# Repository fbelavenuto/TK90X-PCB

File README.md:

# TK90X-PCB

Recriação da placa de circuito impresso do microcomputador de 8 bits TK90X da Microdigital. Projeto iniciado em setembro de 2020.

## Agradecimentos

Agradecimentos ao Daniel Viana (Danjovic) pelo desenho do esquema no software Eagle, Manoel Carvalho (Neco) pelo encorajamento e scans limpos da PCB e ao grupo [Clube do TK](https://www.facebook.com/groups/clubedotk) do Facebook.

## Revisões

Nesse repositório existem várias revisões relacionadas abaixo, cada revisão contém modificações em relação à revisão anterior.

### Rev. 3

Réplica da placa Rev. 3 da Microdigital (Silk TK90X-B rev 3). Essa versão é para montagem de uma réplica da placa original, sem modificações.

### Rev. 4

As modificações efetuadas são:
- Jumpers de solda para selecionar o tipo de memória DRAM, roteando a alimentação corretamente,
- Jumper de solda para permitir o uso de uma EPROM no lugar da ROM original.

### Rev. 5

As modificações efetuadas são:
- Jumpers de solda nos conectores EAR e MIC para opção de montagem com Jacks P2 mono ou estéreo e saída de áudio no conector MIC
-  Desativação do circuito de RF dando lugar a uma saída de vídeo-composto on-board e conector RCA próprio.

Essa revisão não é encorajada a ser fabricada.

### Rev. 6

As modificações efetuadas são:
- Alteração no IC10 para corrigir a leitura da porta 254, compatibilizando esta porta com o padrão ZX e permitindo a execução de mais softwares.

Alguns componentes não precisam ser montados pela extinção do circuito de RF, veja a documentação específica na pasta *Docs* da revisão.

### Rev. 7

As modificações efetuadas são:
- Alteração nos componentes do circuito de vídeo:
  - Retirados os componentes não necessários referente ao circuito de RF,
  - IC12 foi rotacionado para abrir espaço para um conector RCA extra.
- Adicionado conectores dupont/pinheader:
  - Botão de RESET externo,
  - Chave para seleção de frequência vertical da ULA,
  - LED para uso no gabinete do TK95.
- Jumper de solda para seleção do tipo de sinal de vídeo a ser codificado (NTSC ou PAL/PAL-M) de acordo com o valor de cristal escolhido.
- Jumper de solda para permitir a ligação do sinal necessário para uso da interface [TK-MEM 128K](http://www.luccas.com.br/index.php/8-bits/artigos/23-preparando-o-tk90x-tk95-para-a-tkmem-128).

O conector RCA extra está posicionado no mesmo lugar da saída de RF do ZX Spectrum original, permitindo a montagem da placa dentro do seu gabinete original. Este conector extra é configurado por um jumper de solda que permite mapear o sinal de vídeo ou o sinal de áudio dando a opção de colocar um segundo RCA adaptando o case de um TK90X e ter saída de áudio em RCA.

# Pastas

*Common* possui arquivos referentes a todas as revisões.

Dentro de cada pasta de cada revisão há três subpastas com os nomes *Docs*, *Eagle* e *Gerber*. O esquema elétrico em PDF, imagens, lista de materiais, etc, estão em *Docs*. Na subpasta *Eagle* há os arquivos originais para a versão 9 do software Autodesk Eagle. Para a confecção das placas há os arquivos em formato gerber na pasta *Gerber* que podem ser enviados para uma empresa de fabricação de PCBs.

Para a Rev.7 abra o arquivo [ibom.html](Rev7/Docs/ibom.html) localmente ou acesse [este link](https://fbelavenuto.github.io/pages/TK90X-PCB-Rev7-ibom.html) para visualizar os componentes e seus lugares na placa. Criado com o projeto [InteractiveHtmlBom](https://github.com/openscopeproject/InteractiveHtmlBom), linha de comando: `generate_interactive_bom --highlight-pin1 all --blacklist-empty-val TK90X.brd`

# Observações

É encorajado a fabricação da Rev. 7 por conter mais opções de configuração e correções de problemas conhecidos.

É recomendado a fabricação com finalização ENIG ou ouro no conector Edge para mais durabilidade.

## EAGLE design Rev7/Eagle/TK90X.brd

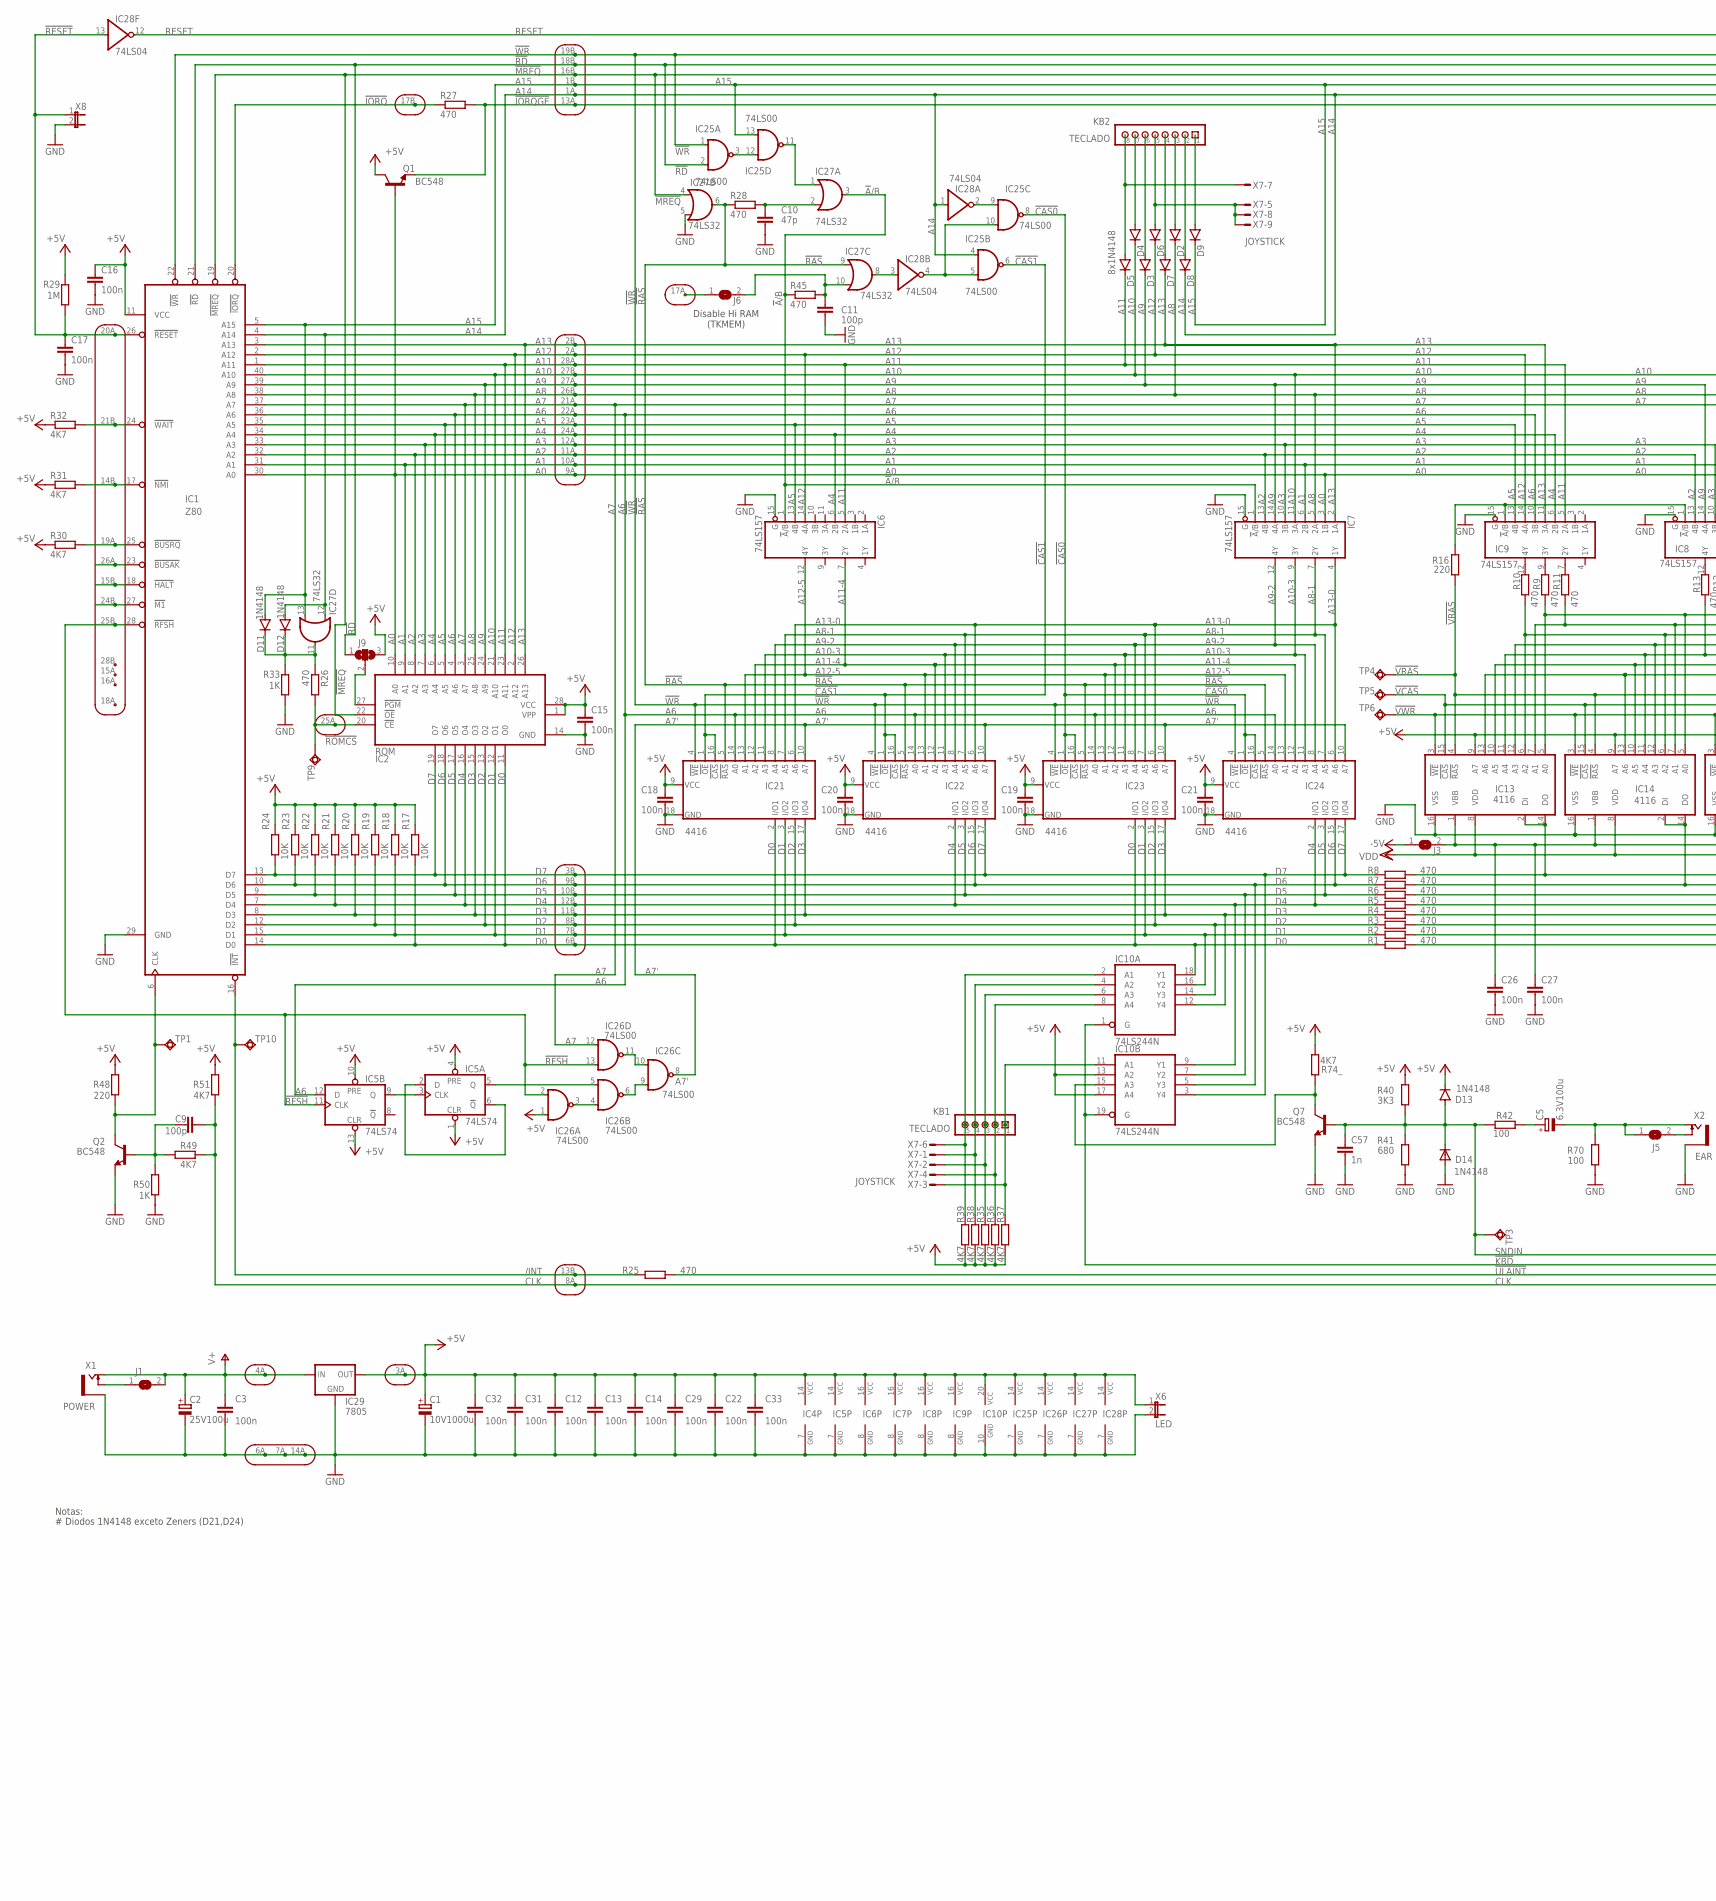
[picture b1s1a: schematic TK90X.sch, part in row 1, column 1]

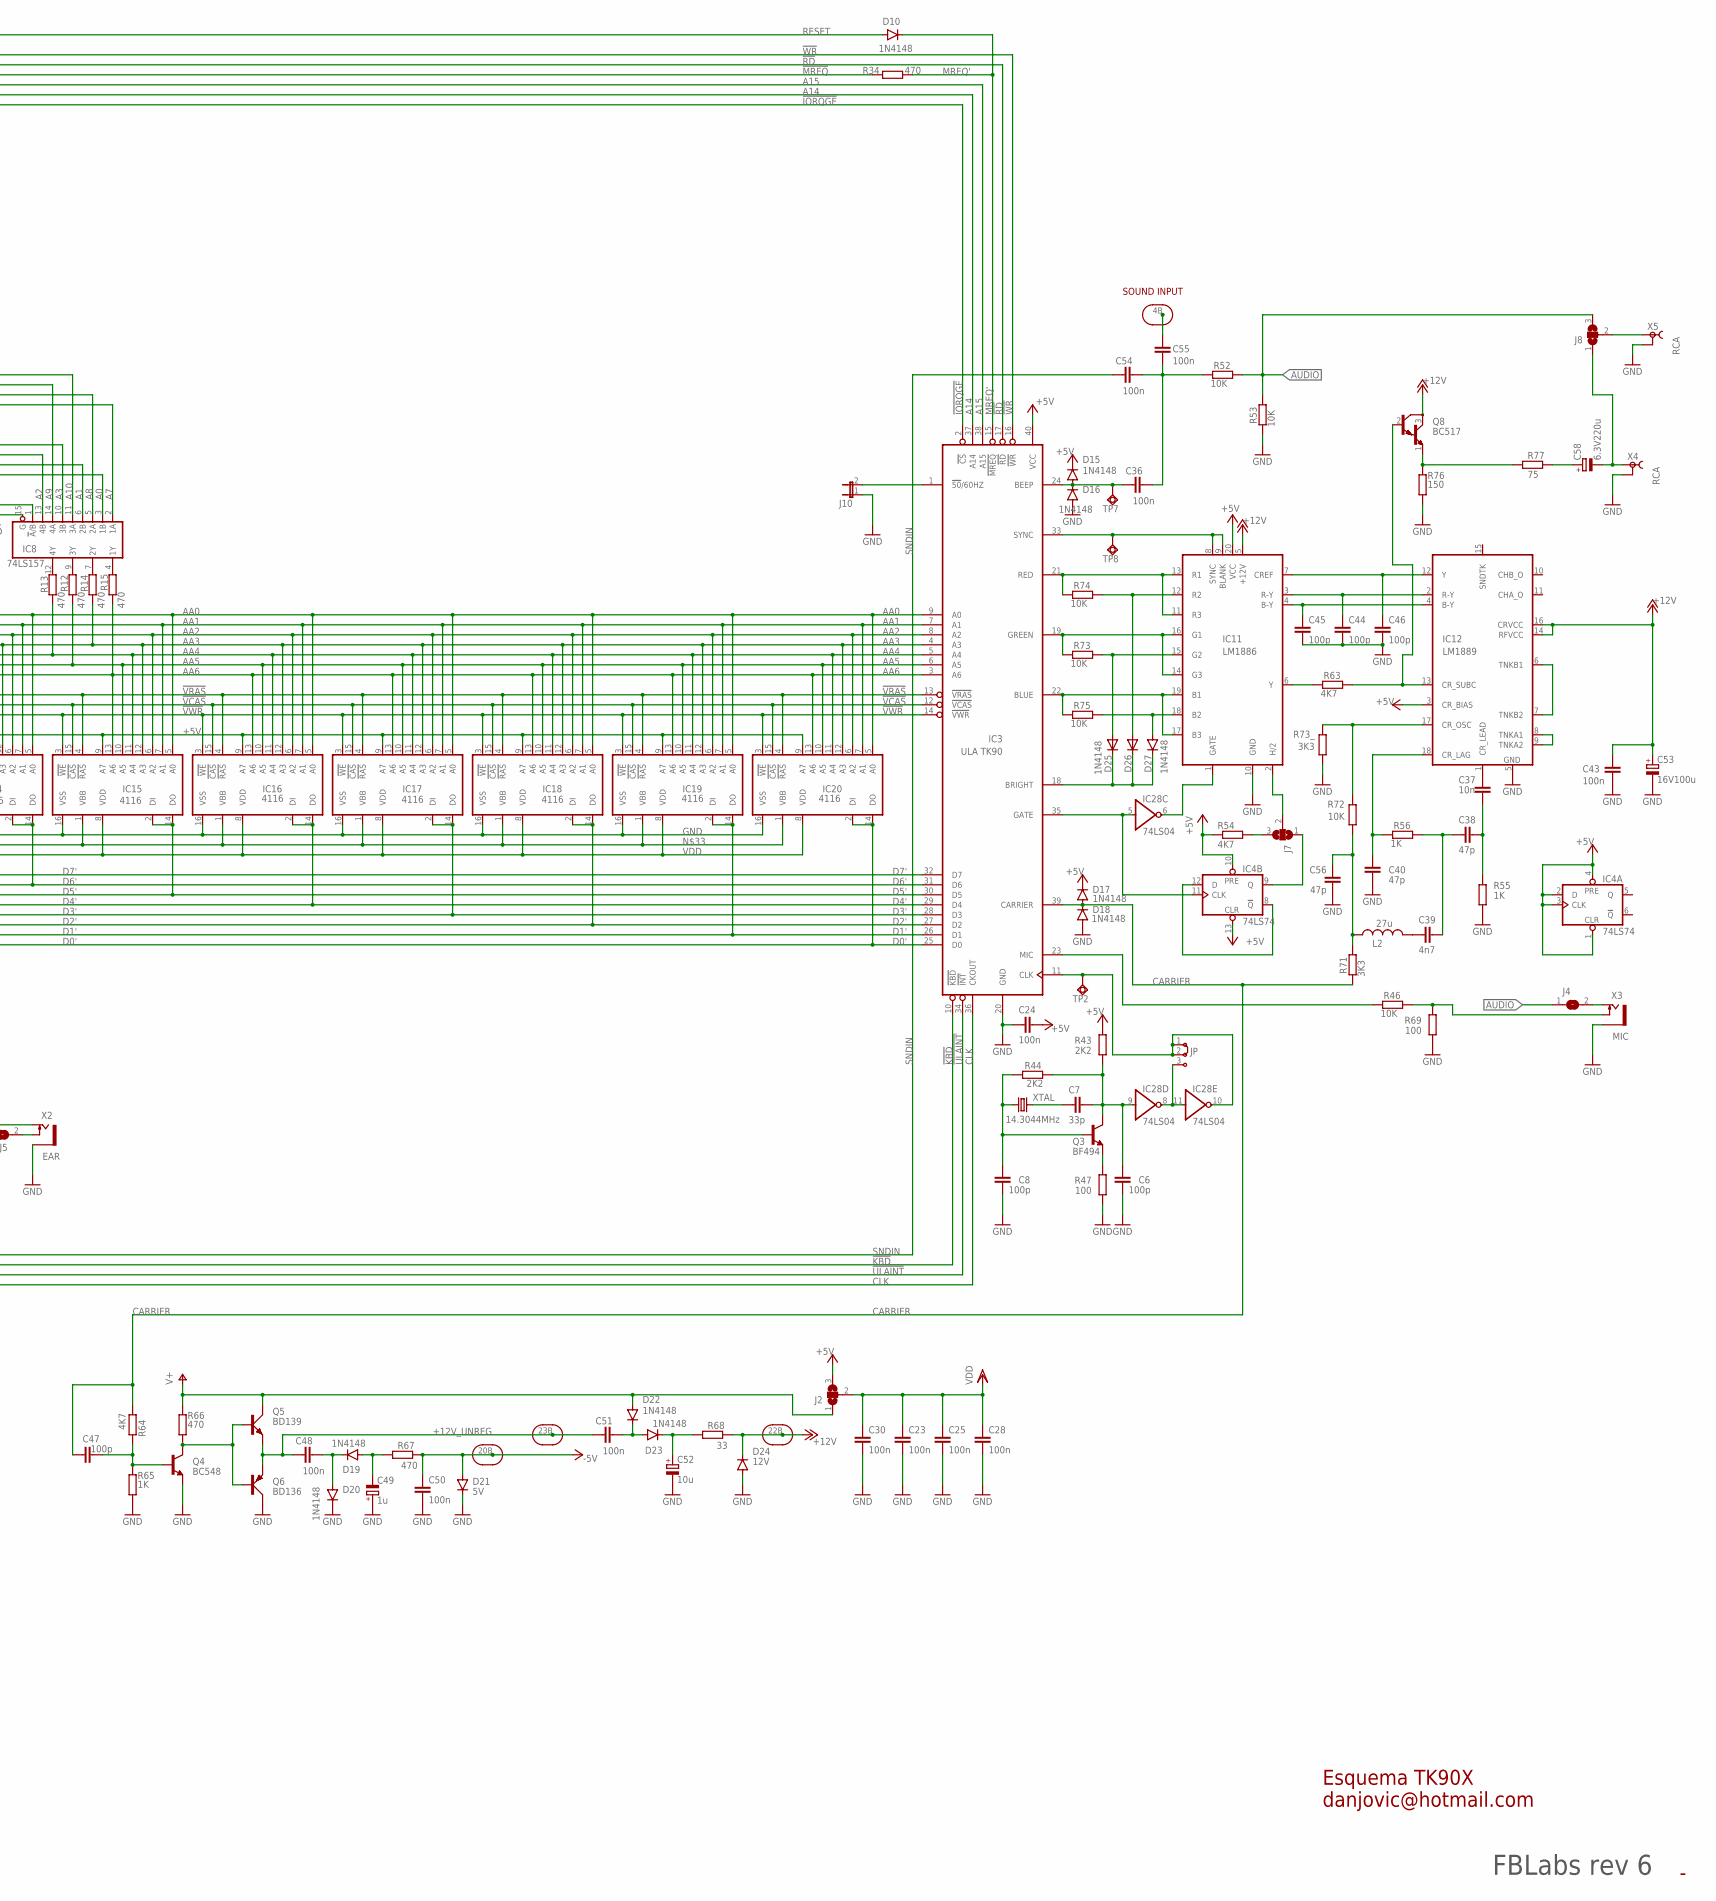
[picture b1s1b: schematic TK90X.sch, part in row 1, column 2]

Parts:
C1: 10V1000u; E5-8,5
C2: 25V100u; E5-6
C3, C12, C13, C14, C15, C16, C17, C18, C19, C20, C21, C22, C23, C24, C25, C26, C27, C28, C29, C30, C31, C32, C33, C36, C43, C48, C50, C51, C54, C55: 100n; C050-024X044
C5: 6.3V100u; E5-4
C6, C8, C9, C11, C44, C45, C46, C47: 100p; C050-024X044
C7: 33p; C050-024X044
C10, C38, C40, C56: 47p; C050-024X044
C37: 10n; C050-024X044
C39: 4n7; C050-024X044
C49: 1u; E2-4
C52: 10u; E2-4
C53: 16V100u; E5-5
C57: 1n; C050-024X044
C58: 6.3V220u; E5-6
D2, D3, D4, D5, D6, D7, D8, D9, D10, D11, D12, D13, D15, D16, D17, D18, D19, D20, D22, D23, D27: 1N4148; DO35-12
D14, D25, D26: 1N4148; D-5
D21: 5V; DO35-12
D24: 12V; DO35-12
IC1: Z80; DIL40
IC2: ROM; DIL28
IC3: ULA TK90; DIL40
IC4, IC5: 74LS74; DIL14
IC6, IC7, IC8, IC9: 74LS157; DIL16
IC10: 74LS244N; DIL20
IC11: LM1886; DIL20
IC12: LM1889; DIL18
IC13, IC14, IC15, IC16, IC17, IC18, IC19, IC20: 4116; DIL16
IC21, IC22, IC23, IC24: 4416; DIL18
IC25, IC26: 74LS00; DIL14
IC27: 74LS32; DIL14
IC28: 74LS04; DIL14
IC29: 7805; 78XXL
J1, J3, J4, J5, J6: SJ
J2, J7, J8, J9: SJ2W; SJ_2
J10: JP1E; JP1
JP: J2X1MM; 03C
KB1: TECLADO; FE05-1
KB2: TECLADO; FE08
L2: 27u; 0207/7
Q1, Q2, Q4, Q7: BC548; TO92L
Q3: BF494; TO92-CEB
Q5: BD139; TO126AV
Q6: BD136; TO126AV
Q8: BC517; TO92
R1, R2, R3, R4, R5, R6, R7, R8, R9, R10, R11, R12, R13, R14, R15, R25, R26, R27, R28, R34, R45, R66, R67: 470; 0207/12
R16, R48: 220; 0207/12
R17, R18, R19, R20, R21, R22, R23, R24, R46, R75: 10K; 0207/12
R29: 1M; 0207/12
R30, R31, R32, R35, R36, R37, R38, R39, R49, R51, R54, R63, R64, R74_: 4K7; 0207/12
R33, R50, R65: 1K; 0207/12
R40: 3K3; 0207/12
R41: 680; 0207/5V
R42, R69, R70: 100; 0207/5V
R43, R44: 2K2; 0207/12
R47: 100; 0207/12
R52, R53, R72, R73, R74: 10K; 0207/5V
R55, R56: 1K; 0207/5V
R68: 33; 0207/12
R71, R73_: 3K3; 0207/5V
R76: 150; 0207/5V
R77: 75; 0207/5V
TP1, TP2, TP3, TP4, TP5, TP6, TP7, TP8, TP9, TP10: TPSQPAD1-13; P1-13
U$1: TK90_EDGE; TK-EDGE
X1: POWER; P2S
X2: EAR; P2S
X3: MIC; P2S
X4, X5: RCA; DX1
X6: LED; JP1
X7: JOYSTICK; 177-009-MALE
X8: JP1E; JP1
XTAL: 14.3044MHz; HC49/S

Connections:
!A!/B: IC6.1 (!A!/B), IC7.1 (!A!/B), IC27.3 (O), R45.1
!BUSAK: IC1.23 (!BUSAK), U$1.26A
!BUSRQ: IC1.25 (!BUSRQ), R30.2, U$1.19A
!CAS0: IC23.1 (!OE), IC23.16 (!CAS), IC24.1 (!OE), IC24.16 (!CAS), IC25.8 (O)
!CAS1: IC21.1 (!OE), IC21.16 (!CAS), IC22.1 (!OE), IC22.16 (!CAS), IC25.6 (O)
!HALT: IC1.18 (!HALT), U$1.15B
!IORQ: IC1.20 (!IORQ), R27.1, U$1.17B
!IORQGE: IC3.2 (!CS), Q1.1 (E), R27.2, U$1.13A
!KBD: IC3.10 (!KBD), IC10.1 (G), IC10.19 (G)
!M1: IC1.27 (!M1), U$1.24B
!MREQ: IC1.19 (!MREQ), IC2.22 (!OE), IC27.4 (I0), R34.1, U$1.16B
!NMI: IC1.17 (!NMI), R31.2, U$1.14B
!RAS: IC21.5 (!RAS), IC22.5 (!RAS), IC23.5 (!RAS), IC24.5 (!RAS), IC27.6 (O), IC27.9 (I0), R28.1
!RD: IC1.21 (!RD), IC3.17 (!RD), IC25.2 (I1), J9.1, U$1.18B
!RESET: C17.1, IC1.26 (!RESET), IC28.13 (I), R29.1, U$1.20A, X8.1
!RFSH: IC1.28 (!RFSH), IC5.11 (CLK), IC26.2 (I1), IC26.13 (I1), U$1.25B
!ROMCS: IC2.20 (!CE), R26.2, TP9.TP, U$1.25A
!ULAINT: IC3.34 (!INT), R25.1
!VCAS: IC3.12 (!VCAS), IC13.15 (!CAS), IC14.15 (!CAS), IC15.15 (!CAS), IC16.15 (!CAS), IC17.15 (!CAS), IC18.15 (!CAS), IC19.15 (!CAS), IC20.15 (!CAS), TP5.TP
!VRAS: IC3.13 (!VRAS), IC13.4 (!RAS), IC14.4 (!RAS), IC15.4 (!RAS), IC16.4 (!RAS), IC17.4 (!RAS), IC18.4 (!RAS), IC19.4 (!RAS), IC20.4 (!RAS), R16.2, TP4.TP
!VWR: IC3.14 (!VWR), IC13.3 (!WE), IC14.3 (!WE), IC15.3 (!WE), IC16.3 (!WE), IC17.3 (!WE), IC18.3 (!WE), IC19.3 (!WE), IC20.3 (!WE), TP6.TP
!WAIT: IC1.24 (!WAIT), R32.2, U$1.21B
!WR: IC1.22 (!WR), IC3.16 (!WR), IC21.4 (!WE), IC22.4 (!WE), IC23.4 (!WE), IC24.4 (!WE), IC25.1 (I0), U$1.19B
+5V: C1.+, C12.2, C13.2, C14.2, C15.1, C16.1, C18.1, C19.1, C20.1, C21.1, C22.2, C24.2, C29.2, C31.2, C32.2, C33.2, D13.C (K), D15.C (K), D17.C (K), IC1.11 (VCC), IC2.1 (VPP), IC2.28 (VCC), IC3.40 (VCC), IC4.1 (CLR), IC4.2 (D), IC4.3 (CLK), IC4.4 (PRE), IC4.10 (PRE), IC4.13 (CLR), IC4.14 (VCC), IC5.1 (CLR), IC5.4 (PRE), IC5.10 (PRE), IC5.13 (CLR), IC5.14 (VCC), IC6.16 (VCC), IC7.16 (VCC), IC8.16 (VCC), IC9.16 (VCC), IC10.13 (A2), IC10.17 (A4), IC10.20 (VCC), IC11.20 (VCC), IC12.3 (CR_BIAS), IC13.9 (A7), IC14.9 (A7), IC15.9 (A7), IC16.9 (A7), IC17.9 (A7), IC18.9 (A7), IC19.9 (A7), IC20.9 (A7), IC21.9 (VCC), IC22.9 (VCC), IC23.9 (VCC), IC24.9 (VCC), IC25.14 (VCC), IC26.1 (I0), IC26.14 (VCC), IC27.14 (VCC), IC28.14 (VCC), IC29.OUT, J2.3, J9.3, Q1.3 (C), R17.2, R18.2, R19.2, R20.2, R21.2, R22.2, R23.2, R24.2, R29.2, R30.1, R31.1, R32.1, R35.1, R36.1, R37.1, R38.1, R39.1, R40.2, R43.2, R48.2, R51.2, R54.1, R74_.2, U$1.3A, X6.1
+12V: C43.2, C53.+, D24.C (K), IC11.5 (+12V), IC12.14 (RFVCC), IC12.16 (CRVCC), Q8.3 (C), R68.1, U$1.22B
+12V_UNREG: C48.1, C51.1, Q5.E, Q6.E, U$1.23B
-5V: C50.1, D21.A, J3.1, R67.1, U$1.20B
/INT: IC1.16 (!INT), R25.2, TP10.TP, U$1.13B
A0: IC1.30 (A0), IC2.10 (A0), IC7.3 (1B), IC8.3 (1B), Q1.2 (B), U$1.9A
A1: IC1.31 (A1), IC2.9 (A1), IC7.6 (2B), IC8.6 (2B), U$1.10A
A2: IC1.32 (A2), IC2.8 (A2), IC7.13 (4B), IC8.13 (4B), U$1.11A
A3: IC1.33 (A3), IC2.7 (A3), IC7.10 (3B), IC8.10 (3B), U$1.12A
A4: IC1.34 (A4), IC2.6 (A4), IC6.6 (2B), IC9.6 (2B), U$1.24A
A5: IC1.35 (A5), IC2.5 (A5), IC6.13 (4B), IC9.13 (4B), U$1.23A
A6: IC1.36 (A6), IC2.4 (A6), IC5.12 (D), IC9.10 (3B), IC21.14 (A0), IC22.14 (A0), IC23.14 (A0), IC24.14 (A0), U$1.22A
A7: IC1.37 (A7), IC2.3 (A7), IC8.2 (1A), IC26.12 (I0), U$1.21A
A7': IC21.10 (A7), IC22.10 (A7), IC23.10 (A7), IC24.10 (A7), IC26.8 (O)
A8: D2.C (K), IC1.38 (A8), IC2.25 (A8), IC7.5 (2A), IC8.5 (2A), U$1.26B
A8-1: IC7.7 (2Y), IC21.7 (A5), IC22.7 (A5), IC23.7 (A5), IC24.7 (A5)
A9: D3.C (K), IC1.39 (A9), IC2.24 (A9), IC7.14 (4A), IC8.14 (4A), U$1.27A
A9-2: IC7.12 (4Y), IC21.8 (A4), IC22.8 (A4), IC23.8 (A4), IC24.8 (A4)
A10: D4.C (K), IC1.40 (A10), IC2.21 (A10), IC7.11 (3A), IC8.11 (3A), U$1.27B
A10-3: IC7.9 (3Y), IC21.11 (A3), IC22.11 (A3), IC23.11 (A3), IC24.11 (A3)
A11: D5.C (K), IC1.1 (A11), IC2.23 (A11), IC6.5 (2A), IC9.5 (2A), U$1.28A
A11-4: IC6.7 (2Y), IC21.12 (A2), IC22.12 (A2), IC23.12 (A2), IC24.12 (A2)
A12: D6.C (K), IC1.2 (A12), IC2.2 (A12), IC6.14 (4A), IC9.14 (4A), U$1.2A
A12-5: IC6.12 (4Y), IC21.13 (A1), IC22.13 (A1), IC23.13 (A1), IC24.13 (A1)
A13: D7.C (K), IC1.3 (A13), IC2.26 (A13), IC7.2 (1A), IC9.11 (3A), U$1.2B
A13-0: IC7.4 (1Y), IC21.6 (A6), IC22.6 (A6), IC23.6 (A6), IC24.6 (A6)
A14: D8.C (K), D12.A, IC1.4 (A14), IC3.37 (A14), IC25.4 (I0), IC27.12 (I0), IC28.1 (I), U$1.1A
A15: D9.C (K), D11.A, IC1.5 (A15), IC3.38 (A15), IC25.13 (I1), IC27.13 (I1), U$1.1B
AA0: IC3.9 (A0), IC13.5 (A0), IC14.5 (A0), IC15.5 (A0), IC16.5 (A0), IC17.5 (A0), IC18.5 (A0), IC19.5 (A0), IC20.5 (A0), R9.1
AA1: IC3.7 (A1), IC13.7 (A1), IC14.7 (A1), IC15.7 (A1), IC16.7 (A1), IC17.7 (A1), IC18.7 (A1), IC19.7 (A1), IC20.7 (A1), R11.1
AA2: IC3.8 (A2), IC13.6 (A2), IC14.6 (A2), IC15.6 (A2), IC16.6 (A2), IC17.6 (A2), IC18.6 (A2), IC19.6 (A2), IC20.6 (A2), R10.1
AA3: IC3.4 (A3), IC13.12 (A3), IC14.12 (A3), IC15.12 (A3), IC16.12 (A3), IC17.12 (A3), IC18.12 (A3), IC19.12 (A3), IC20.12 (A3), R14.1
AA4: IC3.5 (A4), IC13.11 (A4), IC14.11 (A4), IC15.11 (A4), IC16.11 (A4), IC17.11 (A4), IC18.11 (A4), IC19.11 (A4), IC20.11 (A4), R13.1
AA5: IC3.6 (A5), IC13.10 (A5), IC14.10 (A5), IC15.10 (A5), IC16.10 (A5), IC17.10 (A5), IC18.10 (A5), IC19.10 (A5), IC20.10 (A5), R12.1
AA6: IC3.3 (A6), IC13.13 (A6), IC14.13 (A6), IC15.13 (A6), IC16.13 (A6), IC17.13 (A6), IC18.13 (A6), IC19.13 (A6), IC20.13 (A6), R15.1
AUDIO: J4.1, J8.3, R52.1, R53.1
BEEP: C36.1, D15.A, D16.C (K), IC3.24 (BEEP), TP7.TP
CARRIER: C47.1, D17.A, D18.C (K), IC3.39 (CARRIER), R64.2, R71.2
CLK: C9.2, IC3.36 (CKOUT), R49.2, R51.1, U$1.8A
D0: IC1.14 (D0), IC2.11 (O0), IC10.18 (Y1), IC21.2 (I/O1), IC23.2 (I/O1), R1.2, R17.1, U$1.6B
D0': IC3.25 (D0), IC20.2 (DI), IC20.14 (DO), R1.1
D1: IC1.15 (D1), IC2.12 (O1), IC10.16 (Y2), IC21.3 (I/O2), IC23.3 (I/O2), R2.2, R18.1, U$1.7B
D1': IC3.26 (D1), IC19.2 (DI), IC19.14 (DO), R2.1
D2: IC1.12 (D2), IC2.13 (O2), IC10.14 (Y3), IC21.15 (I/O3), IC23.15 (I/O3), R3.2, R19.1, U$1.8B
D2': IC3.27 (D2), IC18.2 (DI), IC18.14 (DO), R3.1
D3: IC1.8 (D3), IC2.15 (O3), IC10.12 (Y4), IC21.17 (I/O4), IC23.17 (I/O4), R4.2, R20.1, U$1.11B
D3': IC3.28 (D3), IC17.2 (DI), IC17.14 (DO), R4.1
D4: IC1.7 (D4), IC2.16 (O4), IC10.9 (Y1), IC22.2 (I/O1), IC24.2 (I/O1), R5.2, R21.1, U$1.12B
D4': IC3.29 (D4), IC16.2 (DI), IC16.14 (DO), R5.1
D5: IC1.9 (D5), IC2.17 (O5), IC10.7 (Y2), IC22.3 (I/O2), IC24.3 (I/O2), R6.2, R22.1, U$1.10B
D5': IC3.30 (D5), IC15.2 (DI), IC15.14 (DO), R6.1
D6: IC1.10 (D6), IC2.18 (O6), IC10.5 (Y3), IC22.15 (I/O3), IC24.15 (I/O3), R7.2, R23.1, U$1.9B
D6': IC3.31 (D6), IC14.2 (DI), IC14.14 (DO), R7.1
D7: IC1.13 (D7), IC2.19 (O7), IC10.3 (Y4), IC22.17 (I/O4), IC24.17 (I/O4), R8.2, R24.1, U$1.3B
D7': IC3.32 (D7), IC13.2 (DI), IC13.14 (DO), R8.1
D19: C48.2, D19.C (K), D20.A
GND: C1.-, C2.-, C3.1, C6.1, C8.1, C10.2, C11.2, C12.1, C13.1, C14.1, C15.2, C16.2, C17.2, C18.2, C19.2, C20.2, C21.2, C22.1, C23.2, C24.1, C25.2, C26.2, C27.2, C28.2, C29.1, C30.2, C31.1, C32.1, C33.1, C40.1, C43.1, C44.2, C45.2, C46.2, C49.+, C50.2, C52.-, C53.-, C56.1, C57.2, D14.A, D16.A, D18.A, D20.C (K), D21.C (K), D24.A, IC1.29 (GND), IC2.14 (GND), IC3.20 (GND), IC4.7 (GND), IC5.7 (GND), IC6.8 (GND), IC6.15 (G), IC7.8 (GND), IC7.15 (G), IC8.8 (GND), IC8.15 (G), IC9.8 (GND), IC9.15 (G), IC10.10 (GND), IC11.10 (GND), IC12.5 (GND), IC13.16 (VSS), IC14.16 (VSS), IC15.16 (VSS), IC16.16 (VSS), IC17.16 (VSS), IC18.16 (VSS), IC19.16 (VSS), IC20.16 (VSS), IC21.18 (GND), IC22.18 (GND), IC23.18 (GND), IC24.18 (GND), IC25.7 (GND), IC26.7 (GND), IC27.5 (I1), IC27.7 (GND), IC28.7 (GND), IC29.GND, J10.1, Q2.1 (E), Q4.1 (E), Q6.C, Q7.1 (E), R33.2, R41.1, R47.1, R50.1, R53.2, R55.2, R65.2, R69.1, R70.1, R73_.2, R76.2, U$1.6A, U$1.7A, U$1.14A, X1.SLEEVE, X2.SLEEVE, X3.SLEEVE, X4.2, X4.2@1 (2), X4.2@2 (2), X5.2, X5.2@1 (2), X5.2@2 (2), X6.2, X8.2
MREQ': D10.C (K), IC3.15 (!MREQ), R34.2
unnamed: IC5.3 (CLK), IC5.9 (Q)
unnamed: IC5.2 (D), IC5.6 (!Q)
unnamed: IC5.5 (Q), IC26.5 (I1)
unnamed: IC26.3 (O), IC26.4 (I0)
unnamed: IC26.10 (I1), IC26.11 (O)
unnamed: IC26.6 (O), IC26.9 (I0)
unnamed: IC25.3 (O), IC25.12 (I0)
unnamed: IC10.2 (A1), KB1.5, R39.2, X7.6
unnamed: C5.+, R42.1
unnamed: D11.C (K), D12.C (K), IC27.11 (O), R26.1, R33.1
unnamed: C10.1, IC27.2 (I1), R28.2
unnamed: C11.1, IC27.10 (I1), J6.2, R45.2
unnamed: IC25.5 (I1), IC25.10 (I1), IC28.4 (O)
unnamed: IC25.11 (O), IC27.1 (I0)
unnamed: IC27.8 (O), IC28.3 (I)
unnamed: C5.-, J5.1, R70.2, X2.TIP
unnamed: IC9.9 (3Y), R9.2
unnamed: C7.1, XTAL.2
unnamed: IC9.12 (4Y), R10.2
unnamed: IC9.7 (2Y), R11.2
unnamed: IC8.9 (3Y), R12.2
unnamed: IC8.12 (4Y), R13.2
unnamed: IC25.9 (I0), IC28.2 (O)
unnamed: IC10.4 (A2), KB1.4, R38.2, X7.1
unnamed: IC10.6 (A3), KB1.3, R35.2, X7.2
unnamed: C9.1, Q2.2 (B), R49.1, R50.2
unnamed: IC10.8 (A4), KB1.2, R36.2, X7.4
unnamed: IC10.11 (A1), KB1.1, R37.2, X7.3
unnamed: IC10.15 (A3), Q7.3 (C), R74_.1
unnamed: IC8.7 (2Y), R14.2
unnamed: IC8.4 (1Y), R15.2
unnamed: IC8.1 (!A!/B), IC9.1 (!A!/B), R16.1
unnamed: C26.1, C27.1, IC13.1 (VBB), IC14.1 (VBB), IC15.1 (VBB), IC16.1 (VBB), IC17.1 (VBB), IC18.1 (VBB), IC19.1 (VBB), IC20.1 (VBB), J3.2
unnamed: D5.A, KB2.8, X7.7
unnamed: D4.A, KB2.7
unnamed: D3.A, KB2.6
unnamed: Q3.E, R47.2
unnamed: D7.A, KB2.4
unnamed: D2.A, KB2.3
unnamed: D8.A, KB2.2
unnamed: D9.A, KB2.1
unnamed: D6.A, KB2.5, X7.5, X7.8, X7.9
unnamed: C51.2, D22.C (K), D23.A
unnamed: R46.1, R69.2, X3.RING
unnamed: C6.2, C7.2, IC28.9 (I), Q3.C, R43.1, R44.1
unnamed: IC28.8 (O), IC28.11 (I), JP.3
unnamed: IC3.11 (CLK), IC28.10 (O), JP.1, JP.2, TP2.TP
unnamed: Q8.1 (E), R76.1, R77.1
unnamed: IC3.23 (MIC), R46.2
unnamed: J4.2, X3.TIP
unnamed: C47.2, Q4.2 (B), R64.1, R65.1
unnamed: C55.2, U$1.4B
unnamed: Q4.3 (C), Q5.B, Q6.B, R66.2
unnamed: IC3.33 (SYNC), IC11.8 (SYNC), IC11.9 (BLANK), TP8.TP
unnamed: IC3.21 (RED), IC11.11 (R3), IC11.13 (R1), R74.2
unnamed: C49.-, D19.A, R67.2
unnamed: C52.+, D23.C (K), R68.2
unnamed: IC3.19 (GREEN), IC11.14 (G3), IC11.16 (G1), R73.2
unnamed: IC3.35 (GATE), IC4.11 (CLK), IC28.5 (I)
unnamed: IC3.22 (BLUE), IC11.17 (B3), IC11.19 (B1), R75.2
unnamed: D25.A, IC11.15 (G2), R73.1
unnamed: D26.A, IC11.12 (R2), R74.1
unnamed: D27.A, IC11.18 (B2), R75.1
unnamed: D25.C, D26.C, D27.C (K), IC3.18 (BRIGHT)
unnamed: IC4.8 (!Q), IC4.12 (D)
unnamed: IC11.6 (Y), R63.2
unnamed: IC11.1 (GATE), IC28.6 (O)
unnamed: IC11.2 (H/2), J7.2
unnamed: IC12.13 (CR_SUBC), Q8.2 (B), R63.1
unnamed: C46.1, IC11.7 (CREF), IC12.12 (Y)
unnamed: C44.1, IC11.3 (R-Y), IC12.2 (R-Y)
unnamed: C45.1, IC11.4 (B-Y), IC12.4 (B-Y)
unnamed: IC4.9 (Q), J7.1
unnamed: J8.2, X5.1
unnamed: IC12.6 (TNKB1), IC12.7 (TNKB2)
unnamed: C58.+, R77.2
unnamed: IC12.17 (CR_OSC), R72.1, R73_.1
unnamed: C40.2, IC12.18 (CR_LAG), R56.2
unnamed: C56.2, L2.1, R71.1, R72.2
unnamed: C37.2, IC12.1 (CR_LEAD)
unnamed: C38.1, C39.2, R56.1
unnamed: C37.1, C38.2, R55.1
unnamed: C39.1, L2.2
unnamed: IC2.27 (!PGM), J9.2
unnamed: IC12.8 (TNKA1), IC12.9 (TNKA2)
unnamed: J1.1, X1.RING
unnamed: IC3.1 (!50!/60HZ), J10.2
unnamed: J5.2, X2.RING
unnamed: J6.1, U$1.17A
unnamed: J7.3, R54.2
unnamed: C36.2, C54.2, C55.1, R52.2
Q3: C8.2, Q3.B, R44.2, XTAL.1
RESET: D10.A, IC28.12 (O)
SNDIN: C54.1, C57.1, D13.A, D14.C, Q7.2 (B), R40.1, R41.2, R42.2, TP3.TP
V+: C2.+, C3.2, D22.A, IC29.IN, J1.2, J2.1, Q5.C, R66.1, U$1.4A, X1.TIP
VDD: C23.1, C25.1, C28.1, C30.1, IC13.8 (VDD), IC14.8 (VDD), IC15.8 (VDD), IC16.8 (VDD), IC17.8 (VDD), IC18.8 (VDD), IC19.8 (VDD), IC20.8 (VDD), J2.2
VIDEO: C58.-, J8.1, X4.1
Z80CLK: IC1.6 (CLK), Q2.3 (C), R48.1, TP1.TP

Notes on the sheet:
JOYSTICK
Esquema TK90X
danjovic@hotmail.com
SOUND INPUT
Notas:
# Diodos 1N4148 exceto Zeners (D21,D24)
8x1N4148
FBLabs rev 6
Disable Hi RAM (TKMEM)

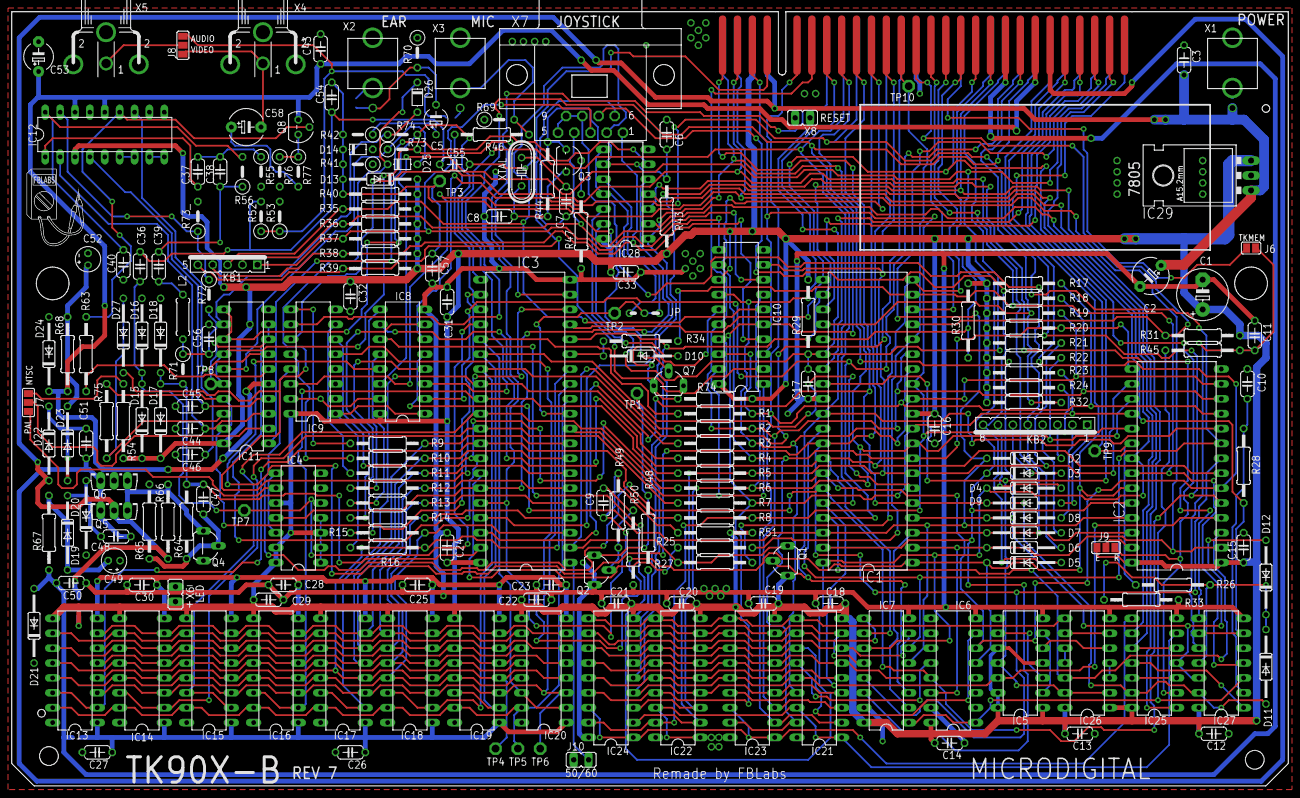
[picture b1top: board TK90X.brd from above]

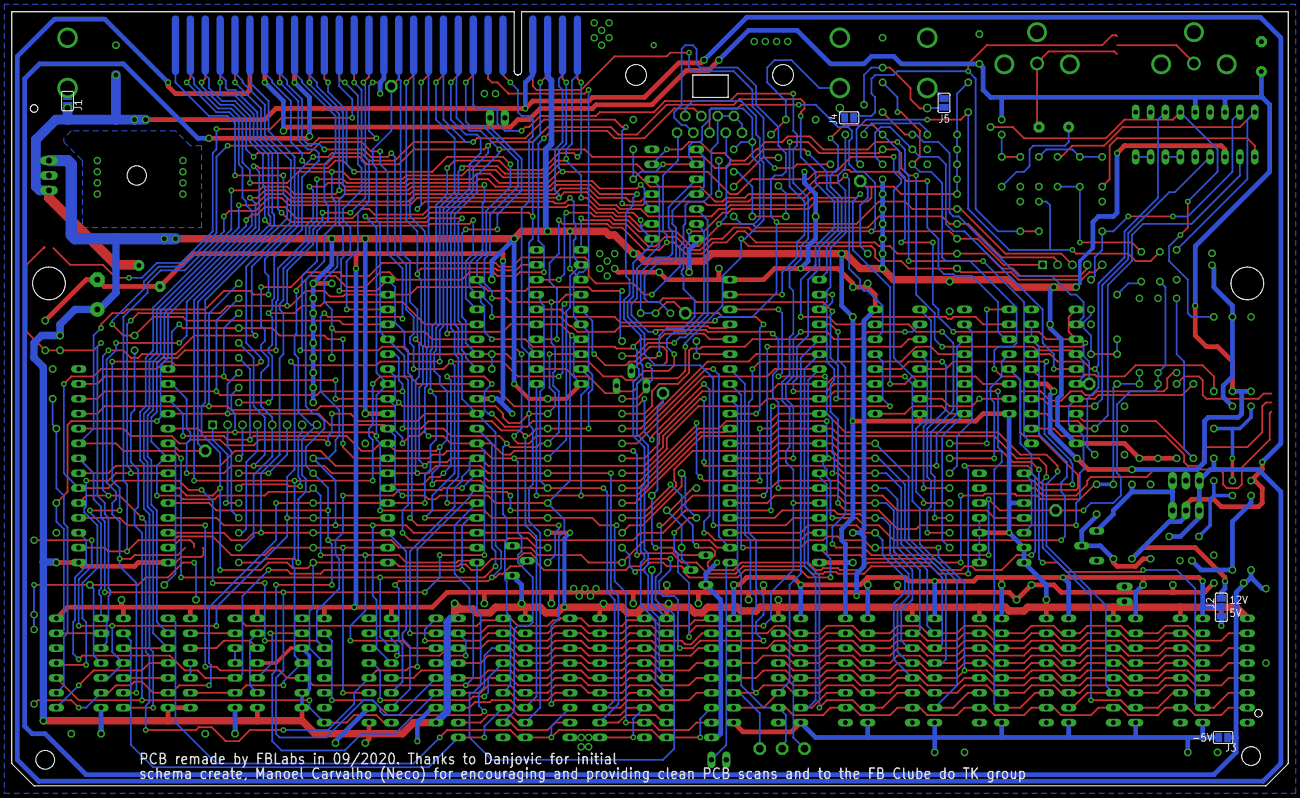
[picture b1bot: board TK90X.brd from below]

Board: 2 copper layers, 217.8 x 132.1 mm, 224 parts (5 on the bottom side), 179 nets.

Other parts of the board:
U$2: LOGO_FABIO_SILK_400MIL

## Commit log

2020-09-29 Upload inicial, placa pronta, necessário testes
2020-10-01 Adicionado mod1 com jumpers para selecionar tensões nas DRAMs 4116
2020-10-02 Mod2 com saída CVBS e áudio no conector estéreo do MIC
2020-10-02 Alguns ajustes no mod2
2020-10-04 Organizado pastas. Rev5 terminado
2020-10-08 Corrigido conexões power Adicionado jumpers de solda pros jacks de áudio Adicionado revisão 6 com 74LS365 substituido pelo 74LS244
2020-11-05 Corrigido BOMs Adicionado revisão 7 com mais configurações e opções
2021-01-02 Adicionado BOM e instruções para a revisão 6
2021-01-02 Organizado BOM_agrupado.txt
2021-01-03 Corrigido valor de R49 e outros pequenos detalhes
2021-02-13 Pequenas correções
2021-04-27 Corrigindo footprint dos jacks RCA Corrigindo lista de peças da revisão 7
2021-04-28 Adicionado fotos da placa Rev 7 montada Alterado instruções para formato Markdown Corrigido capacitor C1 na placa rev. 7 Outras pequenas melhorias e correções
2021-04-29 Adicionado soquetes na lista de material versão em excel. Refeito gerbers e mapa da revisão 7
2021-05-01 Corrigindo posição do conector RCA extra da Rev. 7 Adicionado conteúdo da EPROM Modificado lista de material de Excel para formato Markdown Melhorado documentações
2021-05-23 Corrigido valores de R68 e C52 para melhor geração dos 12V para o Vídeo e DRAMs. Corrigido largura de algumas trilhas
2024-02-20 Adicionado Interactive BOM para a Revisão 7
2024-02-21 Adicionado link para Github pages
